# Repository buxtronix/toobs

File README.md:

# TOOBS - valve headphone amplifier

A low voltage valve headphone amplifier, based off a simple design
from [Rogers Gomez](https://diyaudioprojects.com/Solid/12AU7-IRF510-LM317-Headamp/).

## Features/specs

- Power: 12vDC <1A
- Frequency response: 15-20kHz +- 2dB
- Input: RCA or 3.5mm stereo, mic passthrough.
- Media control support (via 3.5mm TRRS)
- Output: 3.5mm stereo
- Output protetion: ~5s power-on delay
- BoM cost: ~$45AUD (without 12AU7)

## 3d PCB view

See it [here](https://buxtronix.github.io/toobs/3d/trrs.html). It will take about 20s to load the model.

*(Code from https://github.com/easyw/vrm360)*

## General notes

See more detailed notes on the general circuit on the [original
page](https://diyaudioprojects.com/Solid/12AU7-IRF510-LM317-Headamp/).

### Media control / mic

The board has 4-pin TRRS connectors, and can support media control and mic
passthrough (not supported when using the RCA inputs).

The 'Control' connector near the right RCA jack can be used for media
control. Just connect buttons between G and +, -, P and these will have
the same functionality as inline media controls on many headphones. Don't
forget you also need a 4-pin 3.5mm patch to the input source.

Bridge J4 if your headphones have a 4-pin TRRS connector and you'd like to
bridge the mic and/or media control buttons. You'll also need a TRRS patch
lead on the input.
If your headphones are only 3-pin but you'd like to use the media controls
on the board, remove J4. If you leave J4 bridged with 3 pin headphones,
the media controls will not work.

### Valve bias

During initial testing, you will need to set the valve anode bias. With 
no source playing, adjust ' R. Bias' whilst measuring the Q1 gate voltage,
such that it's about half the supply voltage (~6v). Do the same for 'L bias'
and measuring the gate of Q2. This adjustment would generally only need to
be done once, and perhaps every few dozen hours of operation.

### Balance

The balance control is intended to adjust for any mismatch on the valve
triodes. With a mono source playing, adjust until the audio is centered.

## Photos (rendered)

Assembled board

PCB front side

PCB back side

Schematic

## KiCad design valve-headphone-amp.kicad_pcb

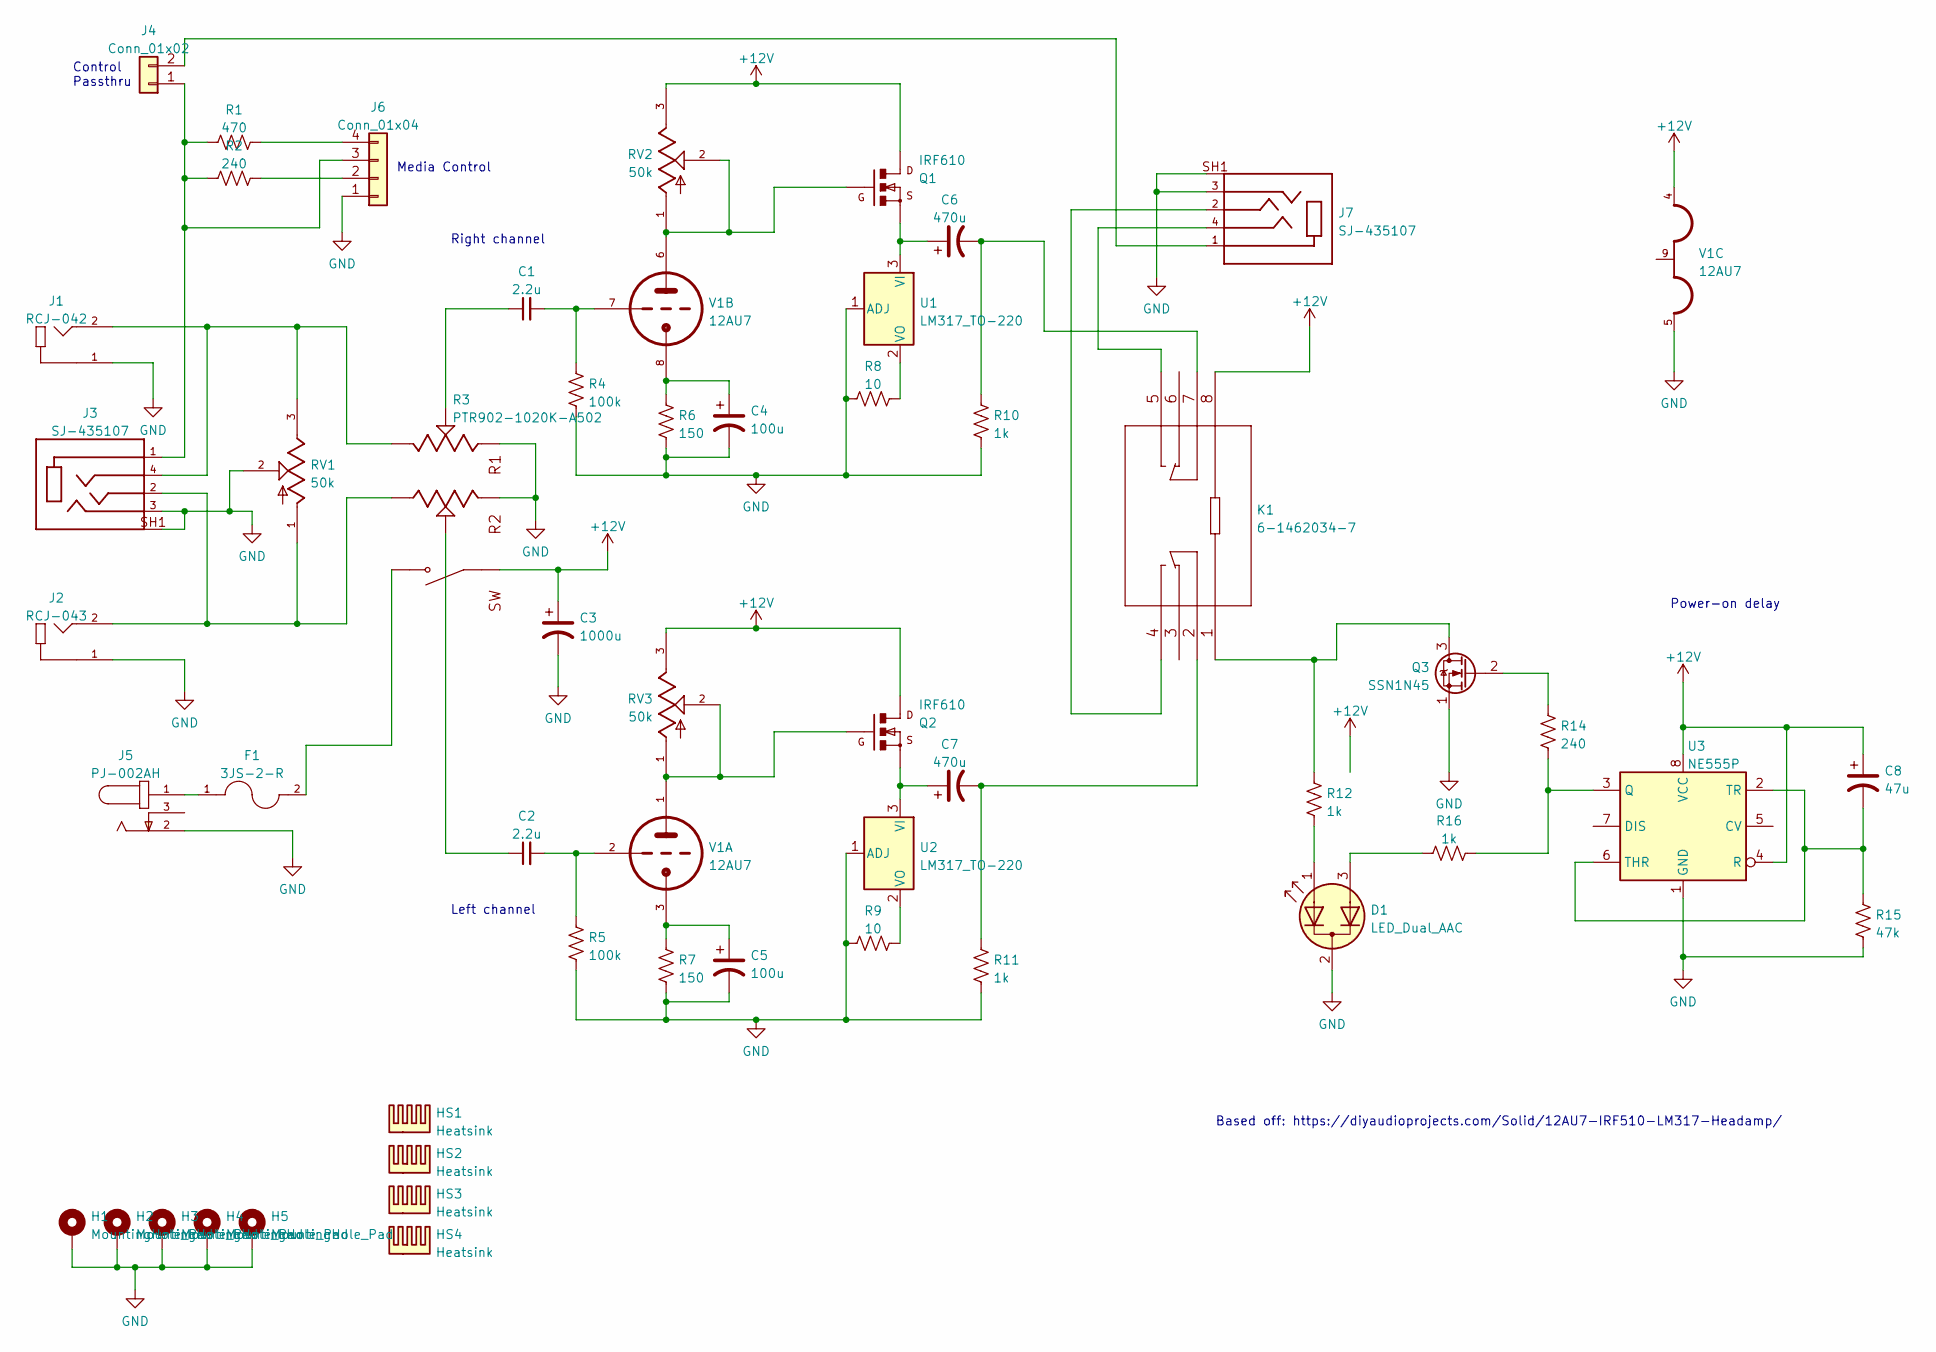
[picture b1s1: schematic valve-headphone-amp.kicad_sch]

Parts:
C1, C2: 2.2u; C_Rect_L7.2mm_W5.5mm_P5.00mm_FKS2_FKP2_MKS2_MKP2
C3: 1000u; CP_10x20mm_horiz-L
C4, C5: 100u; 25ZL100MEFCT16.3X11
C6, C7: 470u; CP_Radial_D10.0mm_P5.00mm
C8: 47u; CP_Radial_D5.0mm_P2.50mm
D1: LED_Dual_AAC; LED_D3.0mm-3
F1: 3JS-2-R; 3JS 1-R; PARTREV 3SB Dec2019
H1, H2, H3, H4, H5: MountingHole_Pad; MountingHole_3.2mm_M3_Pad_Via
HS1, HS2, HS3, HS4: Heatsink; heatsink_19x13mm
J1: RCJ-042; CUI_RCJ-042
J2: RCJ-043; CUI_RCJ-043
J3, J7: SJ-435107; CUI_SJ-435107
J4: Conn_01x02; PinHeader_1x02_P2.54mm_Vertical
J5: PJ-002AH; CUI_PJ-002AH
J6: Conn_01x04; PinHeader_1x04_P2.54mm_Vertical
K1: 6-1462034-7; PC323-12L-X
Q1, Q2: IRF610; TO-220-3_Horizontal_TabDown
Q3: SSN1N45; TO-92_Inline_Wide
R1: 470; R_Axial_DIN0309_L9.0mm_D3.2mm_P12.70mm_Horizontal
R2, R14: 240; R_Axial_DIN0309_L9.0mm_D3.2mm_P12.70mm_Horizontal
R3: PTR902-1020K-A502; TRIM_PTR902-1020K-A502; PARTREV 10/19
R4, R5: 100k; R_Axial_DIN0309_L9.0mm_D3.2mm_P12.70mm_Horizontal
R6, R7: 150; R_Axial_DIN0309_L9.0mm_D3.2mm_P12.70mm_Horizontal
R8, R9: 10; R_Axial_DIN0309_L9.0mm_D3.2mm_P12.70mm_Horizontal
R10, R11, R12: 1k; R_Axial_DIN0309_L9.0mm_D3.2mm_P12.70mm_Horizontal
R15: 47k; R_Axial_DIN0309_L9.0mm_D3.2mm_P5.08mm_Vertical
R16: 1k; R_Axial_DIN0309_L9.0mm_D3.2mm_P5.08mm_Vertical
RV1, RV2, RV3: 50k; Potentiometer_Bourns_3296W_Vertical; PARTREV 08/26/10
U1, U2: LM317_TO-220; TO-220-3_Horizontal_TabDown
U3: NE555P; DIP-8_W7.62mm
V1: 12AU7; socket_gzc9-b

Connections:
+12V: C3.1, C8.1, K1.8, Q1.2, Q2.2, R3.COM, RV2.3, RV3.3, U3.4 (R), U3.8 (VCC), V1.4
GND: C3.2, C4.2, C5.2, D1.2 (K), H1.1, H2.1, H3.1, H4.1, H5.1, J1.1, J2.1, J3.3, J3.SH1 (Shield), J5.2, J6.1, J7.3, J7.SH1 (Shield), Q3.1 (S), R3.R1_1, R3.R2_1, R4.2, R5.2, R6.2, R7.2, R8.1, R9.1, R10.1, R11.1, R15.2, RV1.2, U1.1 (ADJ), U2.1 (ADJ), U3.1 (GND), V1.5
unnamed: C1.1, R3.R1_2
unnamed: C1.2, R4.1, V1.7
unnamed: C2.1, R3.R2_2
unnamed: C2.2, R5.1, V1.2
unnamed: C4.1, R6.1, V1.8
unnamed: C5.1, R7.1, V1.3
unnamed: C6.1, Q1.3, U1.3 (VI)
unnamed: C6.2, K1.7, R10.2
unnamed: C7.1, Q2.3, U2.3 (VI)
unnamed: C7.2, K1.2, R11.2
unnamed: C8.2, R15.1, U3.2 (TR), U3.6 (THR)
unnamed: D1.1 (A1), R12.1
unnamed: F1.1, J5.1
unnamed: F1.2, R3.NO
unnamed: J1.2, J3.4, R3.R1_3, RV1.3
unnamed: J2.2, J3.2, R3.R2_3, RV1.1
unnamed: J3.1, J4.1, J6.3, R1.2, R2.2
unnamed: J4.2, J7.1
unnamed: J6.2, R2.1
unnamed: J6.4, R1.1
unnamed: J7.2, K1.4
unnamed: J7.4, K1.5
unnamed: K1.1, Q3.3 (D), R12.2
unnamed: Q1.1, RV2.1, RV2.2, V1.6
unnamed: Q2.1, RV3.1, RV3.2, V1.1
unnamed: Q3.2 (G), R14.2
unnamed: R8.2, U1.2 (VO)
unnamed: R9.2, U2.2 (VO)
unnamed: R14.1, R16.1, U3.3 (Q)
unnamed: D1.3 (A2), R16.2

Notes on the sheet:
Right channel
Control Passthru
Left channel
Based off: https://diyaudioprojects.com/Solid/12AU7-IRF510-LM317-Headamp/
Media Control
Power-on delay

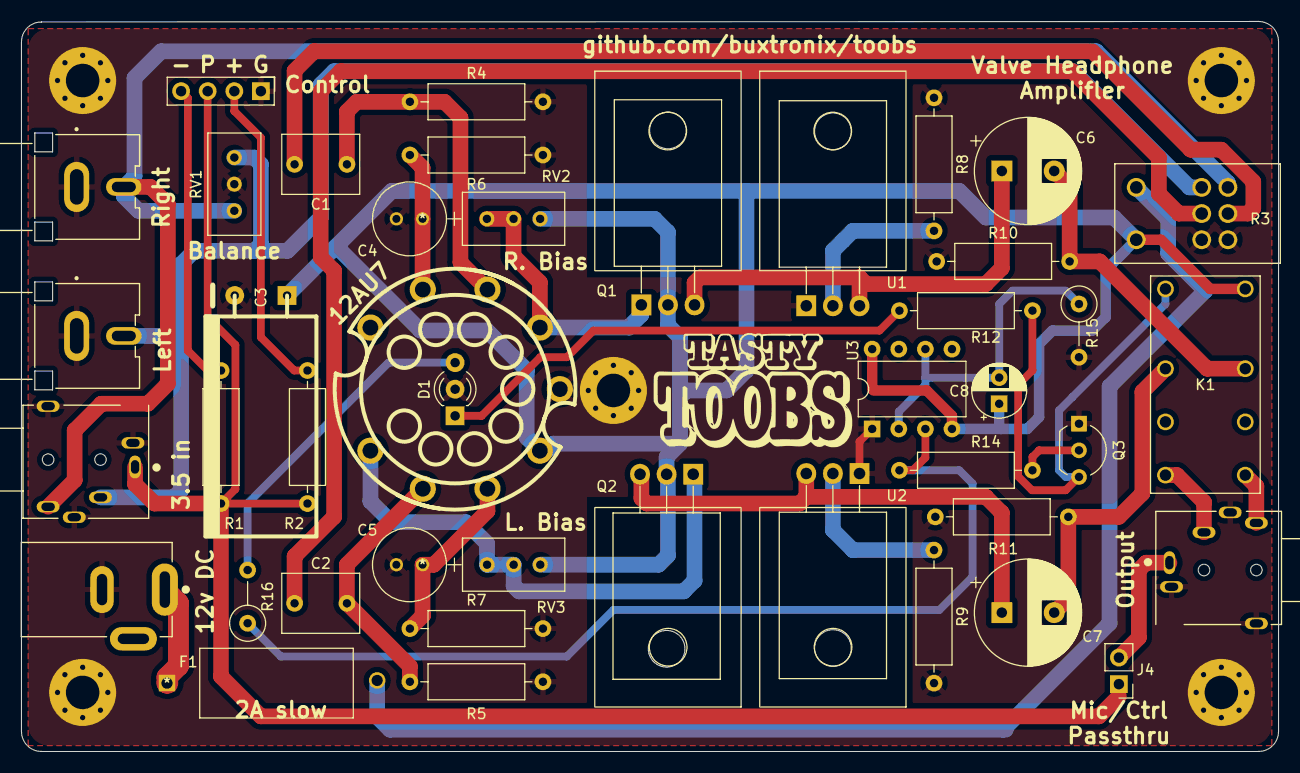
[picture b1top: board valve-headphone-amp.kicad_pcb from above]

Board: 2 copper layers, 120.0 x 69.7 mm, 52 parts (0 on the bottom side), 32 nets.

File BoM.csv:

"Reference(s)","Value","Footprint","PRICE","SUPPLIER_URL"
"C1","2.2u","Capacitor_THT:C_Rect_L7.2mm_W5.5mm_P5.00mm_FKS2_FKP2_MKS2_MKP2","1.84","https://www.digikey.com.au/en/products/detail/kemet/R82CC422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"
"C2","2.2u","Capacitor_THT:C_Rect_L7.2mm_W5.5mm_P5.00mm_FKS2_FKP2_MKS2_MKP2","1.84","https://www.digikey.com.au/en/products/detail/kemet/R82CC422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"
"C3","1000u","w_capacitors:CP_10x20mm_horiz-L","1.25","https://www.digikey.com.au/en/products/detail/rubycon/25ZLS1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"
"C4","100u","rubycon:25ZL100MEFCT16.3X11","0.49","https://www.digikey.com.au/en/products/detail/rubycon/25ZL10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"
"C5","100u","rubycon:25ZL100MEFCT16.3X11","0.49","https://www.digikey.com.au/en/products/detail/rubycon/25ZL10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"
"C6","470u","Capacitor_THT:CP_Radial_D10.0mm_P5.00mm","1.04","https://www.digikey.com.au/en/products/detail/rubycon/25ZLJ4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"
"C7","470u","Capacitor_THT:CP_Radial_D10.0mm_P5.00mm","1.04","https://www.digikey.com.au/en/products/detail/rubycon/25ZLJ4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"
"C8","47u","Capacitor_THT:CP_Radial_D5.0mm_P2.50mm","0.48","https://www.digikey.com.au/en/products/detail/rubycon/25ZLG4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"
"D1","LED_Dual_AAC","LED_THT:LED_D3.0mm-3","0.82","https://www.digikey.com.au/en/products/detail/kingbright/WP1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"
"F1","3JS-2-R","fuses:3JS 1-R","0.67","https://www.digikey.com.au/en/products/detail/bel-fuse-inc/3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"
"H1","MountingHole_Pad","MountingHole:MountingHole_3.2mm_M3_Pad_Via",,
"H2","MountingHole_Pad","MountingHole:MountingHole_3.2mm_M3_Pad_Via",,
"H3","MountingHole_Pad","MountingHole:MountingHole_3.2mm_M3_Pad_Via",,
"H4","MountingHole_Pad","MountingHole:MountingHole_3.2mm_M3_Pad_Via",,
"H5","MountingHole_Pad","MountingHole:MountingHole_3.2mm_M3_Pad_Via",,
"HS1","Heatsink","heatsink:heatsink_19x13mm","0.43","https://www.digikey.com.au/en/products/detail/aavid-thermal-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"
"HS2","Heatsink","heatsink:heatsink_19x13mm","0.43","https://www.digikey.com.au/en/products/detail/aavid-thermal-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"
"HS3","Heatsink","heatsink:heatsink_19x13mm","0.43","https://www.digikey.com.au/en/products/detail/aavid-thermal-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"
"HS4","Heatsink","heatsink:heatsink_19x13mm","0.43","https://www.digikey.com.au/en/products/detail/aavid-thermal-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"
"J1","RCJ-042","rca:CUI_RCJ-042","2.44","https://www.digikey.com.au/en/products/detail/cui-devices/RC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"
"J2","RCJ-043","rca:CUI_RCJ-043","2.44","https://www.digikey.com.au/en/products/detail/cui-devices/RC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"
"J3","SJ-435107","3:CUI_SJ-435107","0.98 USD","https://www.digikey.com.au/en/products/detail/cui-devices/SJ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"
"J4","Conn_01x02","Connector_PinHeader_2.54mm:PinHeader_1x02_P2.54mm_Vertical",,
"J5","PJ-002AH","power:CUI_PJ-002AH","1.19","https://www.digikey.com.au/en/products/detail/cui-devices/PJ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"
"J6","Conn_01x04","Connector_PinHeader_2.54mm:PinHeader_1x04_P2.54mm_Vertical",,
"J7","SJ-435107","3:CUI_SJ-435107","0.98 USD","https://www.digikey.com.au/en/products/detail/cui-devices/SJ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"
"K1","6-1462034-7","footprints:PC323-12L-X","1.90","https://www.digikey.com.au/en/products/detail/picker-compone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"
"Q1","IRF610","Package_TO_SOT_THT:TO-220-3_Horizontal_TabDown","1.46","https://www.digikey.com.au/en/products/detail/vishay-silicon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"
"Q2","IRF610","Package_TO_SOT_THT:TO-220-3_Horizontal_TabDown","1.46","https://www.digikey.com.au/en/products/detail/vishay-silicon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"
"Q3","SSN1N45","Package_TO_SOT_THT:TO-92_Inline_Wide","0.95","https://www.digikey.com.au/en/products/detail/onsemi/SSN1N45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"
"R1","470","Resistor_THT:R_Axial_DIN0309_L9.0mm_D3.2mm_P12.70mm_Horizontal","0.32","https://www.digikey.com.au/en/products/detail/vishay-beyschl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"
"R2","240","Resistor_THT:R_Axial_DIN0309_L9.0mm_D3.2mm_P12.70mm_Horizontal","0.37","https://www.digikey.com.au/en/products/detail/vishay-beyschl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"
"R3","PTR902-1020K-A502","pot:TRIM_PTR902-1020K-A502","6.10","https://www.digikey.com.au/en/products/detail/bourns-inc/PTR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"
"R4","100k","Resistor_THT:R_Axial_DIN0309_L9.0mm_D3.2mm_P12.70mm_Horizontal","0.64","https://www.digikey.com.au/en/products/detail/vishay-beyschl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"
"R5","100k","Resistor_THT:R_Axial_DIN0309_L9.0mm_D3.2mm_P12.70mm_Horizontal","0.64","https://www.digikey.com.au/en/products/detail/vishay-beyschl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"
"R6","150","Resistor_THT:R_Axial_DIN0309_L9.0mm_D3.2mm_P12.70mm_Horizontal","0.36","https://www.digikey.com.au/en/products/detail/vishay-beyschl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"
"R7","150","Resistor_THT:R_Axial_DIN0309_L9.0mm_D3.2mm_P12.70mm_Horizontal","0.36","https://www.digikey.com.au/en/products/detail/vishay-beyschl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"
"R8","10","Resistor_THT:R_Axial_DIN0309_L9.0mm_D3.2mm_P12.70mm_Horizontal","0.36","https://www.digikey.com.au/en/products/detail/vishay-beyschl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"
"R9","10","Resistor_THT:R_Axial_DIN0309_L9.0mm_D3.2mm_P12.70mm_Horizontal","0.36","https://www.digikey.com.au/en/products/detail/vishay-beyschl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"
"R10","1k","Resistor_THT:R_Axial_DIN0309_L9.0mm_D3.2mm_P12.70mm_Horizontal","0.20","https://www.digikey.com.au/en/products/detail/vishay-beyschl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"
"R11","1k","Resistor_THT:R_Axial_DIN0309_L9.0mm_D3.2mm_P12.70mm_Horizontal","0.20","https://www.digikey.com.au/en/products/detail/vishay-beyschl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"
"R12","1k","Resistor_THT:R_Axial_DIN0309_L9.0mm_D3.2mm_P12.70mm_Horizontal","0.20","https://www.digikey.com.au/en/products/detail/vishay-beyschl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"
"R14","240","Resistor_THT:R_Axial_DIN0309_L9.0mm_D3.2mm_P12.70mm_Horizontal","0.37","https://www.digikey.com.au/en/products/detail/vishay-beyschl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"
"R15","47k","Resistor_THT:R_Axial_DIN0309_L9.0mm_D3.2mm_P5.08mm_Vertical","0.29","https://www.digikey.com.au/en/products/detail/vishay-beyschl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"
"R16","1k","Resistor_THT:R_Axial_DIN0309_L9.0mm_D3.2mm_P5.08mm_Vertical","0.20","https://www.digikey.com.au/en/products/detail/vishay-beyschl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"
"RV1","50k","Potentiometer_THT:Potentiometer_Bourns_3296W_Vertical",,"https://www.ebay.com.au/itm/151504157376"
"RV2","50k","Potentiometer_THT:Potentiometer_Bourns_3296W_Vertical",,"https://www.ebay.com.au/itm/151504157376"
"RV3","50k","Potentiometer_THT:Potentiometer_Bourns_3296W_Vertical",,"https://www.ebay.com.au/itm/151504157376"
"U1","LM317_TO-220","Package_TO_SOT_THT:TO-220-3_Horizontal_TabDown","1.23","https://www.digikey.com.au/en/products/detail/onsemi/LM317MA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"
"U2","LM317_TO-220","Package_TO_SOT_THT:TO-220-3_Horizontal_TabDown","1.23","https://www.digikey.com.au/en/products/detail/onsemi/LM317MA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"
"U3","NE555P","Package_DIP:DIP-8_W7.62mm","0.73","https://www.digikey.com.au/en/products/detail/texas-instrume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"
"V1","12AU7","12au7:socket_gzc9-b",,"https://www.ebay.com.au/itm/314046270418"

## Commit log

2022-06-29 TOOBS - initial checkin
2022-06-29 initial 3d viewer checkin
2022-06-29 Add link to 3d model
2022-06-29 Add BoM
2022-07-14 Variant with TRSS jacks and media controls
2022-07-15 Version with TRRS and media button support
2022-07-15 trrs version 3d model
2022-07-15 Add schematic pdf
2022-07-16 Add media
2022-07-16 Fix media
2022-07-18 update 3d model
2022-07-18 fix link to 3d model
2022-07-18 updates, bom
2022-07-22 Add LED for glow
2022-07-22 Update model
2022-08-03 update a bit more
2022-08-03 update render
2022-08-03 pic update
2022-08-05 pcb fab updates
2022-08-26 update parts
2022-08-26 update schematic export

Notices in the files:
parts and their libraries:
Copyright 2021 Accelerated Designs. All rights reserved.
